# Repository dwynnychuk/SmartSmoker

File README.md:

# Smart-Smoker
Upgrade to my existing Traeger smoker BBQ to add intelligent functionality. Initial upgrades target data acquisition to monitor internal and ambient temperatures. The second stage of this project will use integrated sensor data to drive the smoker fan, auger, and hot end with a custom PID-based controller. 

# How it works
Firmware and iOS application in development. The devices will tie into the wall power on the control panel inside the smoker. An iOS device will be used to connect to the system once running, which will receive updates over BLE regarding the status of the cook. 

# Hardware
Main PCB  
- Custom implementation of ESP32-WROOM module for WiFi and BLE connectivity
- AC/DC rectifier with optional USB power handled with power path selector IC (LTC4412)
- Input for 4x K-Type thermocouples to monitor food temperature (x2), external ambient temperature, and internal ambient temperature. Analog multiplexer is used to allow the use of a single amplifier.
- Interface to connect to Lid and Hopper PCBs

Lid PCB  
- Ambient light sensor to detect if the user left the cover off after a cook
- IMU to be used as a forward feed input for the PID controller

Hopper PCB  
- Ambient light sensor to detect if the user left the cover off after a cook
- IMU to alert the user if the hopper lid is left open
- ToF sensor to read remaining pellet level

# Pinout
1 - I2C SDA  
2 - GND  
3 - I2C SCL  
4 - +3.3V  

# Image

# Suggested Changes for Next Hardware REV
- Delete 1x ambient light sensors
- Add a dedicated GND pin for easier use of a logic analyzer
- Breakout XSHUT and INT pins on main board for easier connection to hopper
- Footprint change on U4
- Add control for Traeger interface to implement PID control
- Add jumper for I2C select on IMU(s)

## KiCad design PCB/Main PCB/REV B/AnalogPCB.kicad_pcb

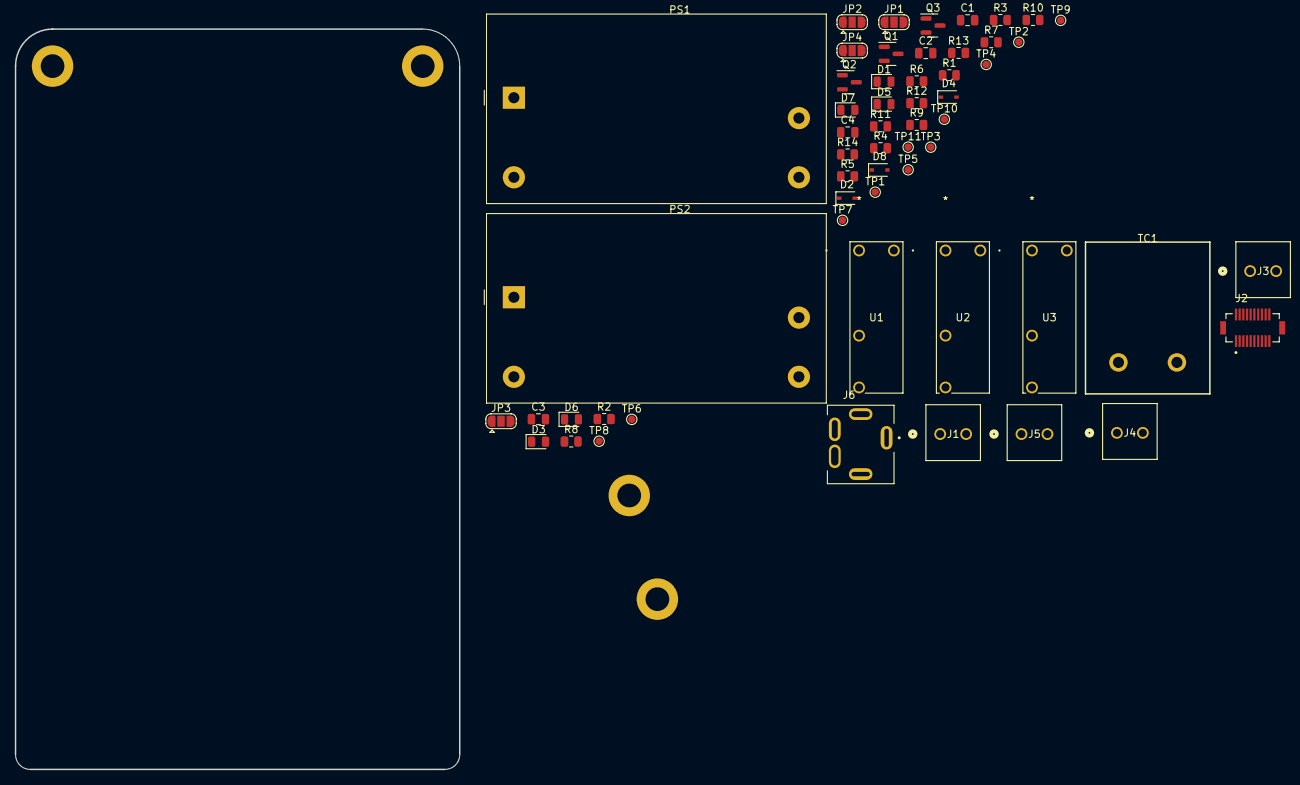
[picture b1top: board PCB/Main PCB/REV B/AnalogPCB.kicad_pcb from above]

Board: 2 copper layers, 60.0 x 100.0 mm, 60 parts (0 on the bottom side), 31 nets, no tracks yet.

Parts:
C1, C3: 0.1uF 50V X7R 0805; C_0805_2012Metric
C2, C4: 10uF 16V X5R 0805; C_0805_2012Metric
D1, D3, D7: B 3.2V 20mA 0805; LED_0805_2012Metric
D2, D4, D8: Schottky 30v 200mA; D_SOD-323
D5, D6: R 2.0V 20mA; LED_0805_2012Metric
H1, H2, H3, H4: MountingHole; MountingHole_3.2mm_M3_DIN965_Pad
J1, J3, J4, J5: 393570002; CONN_393570002_MOL
J2: DF12NB_4.0_-20DP-0.5V_51_; HRS_DF12NB_4.0_-20DP-0.5V_51_
J6: SJ3-35053D; SAMESKY_SJ3-35053D
JP1, JP2, JP3, JP4: SolderJumper_3_Open; SolderJumper-3_P1.3mm_Open_RoundedPad1.0x1.5mm
PS1: IRM-10-3.3; Converter_ACDC_MeanWell_IRM-10-xx_THT
PS2: IRM-05-5; Converter_ACDC_MeanWell_IRM-05-xx_THT
Q1, Q2, Q3: 2N7002; SOT-23
R1, R4, R9: 91Ohm 1% 0805; R_0805_2012Metric
R2, R5, R10: 10K 1% 0805; R_0805_2012Metric
R3, R6, R11: 0 Ohm 0805; R_0805_2012Metric
R7: 150Ohm 1% 0805; R_0805_2012Metric
R8: 64.9Ohm 1% 0805; R_0805_2012Metric
R12, R13, R14: 1kOhm 0.1% 0805; R_0805_2012Metric
TC1: Thermocouple_Block; K-TypeAdapter
TP1, TP2, TP3, TP4, TP5, TP6, TP7, TP8, TP9, TP10, TP11: TP; TestPoint_Pad_D1.0mm
U1, U2, U3: ALDP105W; PAN_ALD_PAN

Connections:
+3.3VA: C1.2, C2.1, J2.1, J2.3, J2.5, J2.7, JP1.3 (B), JP2.3 (B), JP3.3 (B), PS1.4 (+Vo), R8.1, R12.1, R13.1, TP4.1, TP10.1
+5V: C3.2, C4.1, D2.1 (K), D4.1 (K), D8.1 (K), J2.9, J2.11, PS2.4 (+Vo), R1.1, R4.1, R7.1, R9.1, TP5.1, U1.1, U2.1, U3.1
/AC_L: J1.1, PS1.2 (AC/L), PS2.2 (AC/L), TP3.1, U1.2, U2.2, U3.2
/AC_N: J1.2, J3.2, J4.2, J5.2, PS1.1 (AC/N), PS2.1 (AC/N), TP1.1
/Auger_+: J5.1, U1.3
/Fan_+: J4.1, U3.3
/Ignitor_+: J3.1, U2.3
/MeatProbe+: J2.19, R12.2, R14.1
/MeatProbe-: J2.20, J6.3, R13.2
/MeatProbeSleeve: J6.1, JP4.3 (B)
/MeatProbeTip: J6.2, JP4.1 (A)
/Opto_Auger: J2.15, Q1.1 (G), R2.2, TP2.1
/Opto_Fan: J2.16, Q3.1 (G), R10.2, TP9.1
/Opto_Ignitor: J2.17, Q2.1 (G), R5.2, TP6.1
/Probe1+: J2.13, TC1.1 (+)
/Probe1-: J2.14, TC1.2 (-)
GND: C1.1, C2.2, C3.1, C4.2, D5.1 (K), D6.1 (K), J2.2, J2.4, J2.6, J2.8, J2.10, J2.12, J2.18, JP1.1 (A), JP2.1 (A), JP3.1 (A), JP4.2 (C), PS1.3 (-Vo), PS2.3 (-Vo), Q1.2 (S), Q2.2 (S), Q3.2 (S), R14.2, TP11.1
unnamed: D1.1 (K), Q1.3 (D), R3.2
unnamed: D1.2 (A), R1.2
unnamed: D2.2 (A), R3.1, U1.4
unnamed: D3.2 (A), R4.2
unnamed: D5.2 (A), R7.2, TP7.1
unnamed: D7.2 (A), R9.2
unnamed: JP1.2 (C), R2.1
unnamed: JP2.2 (C), R5.1
unnamed: JP3.2 (C), R10.1
unnamed: D3.1 (K), Q2.3 (D), R6.2
unnamed: D7.1 (K), Q3.3 (D), R11.2
unnamed: D6.2 (A), R8.2, TP8.1
unnamed: D4.2 (A), R6.1, U2.4
unnamed: D8.2 (A), R11.1, U3.4

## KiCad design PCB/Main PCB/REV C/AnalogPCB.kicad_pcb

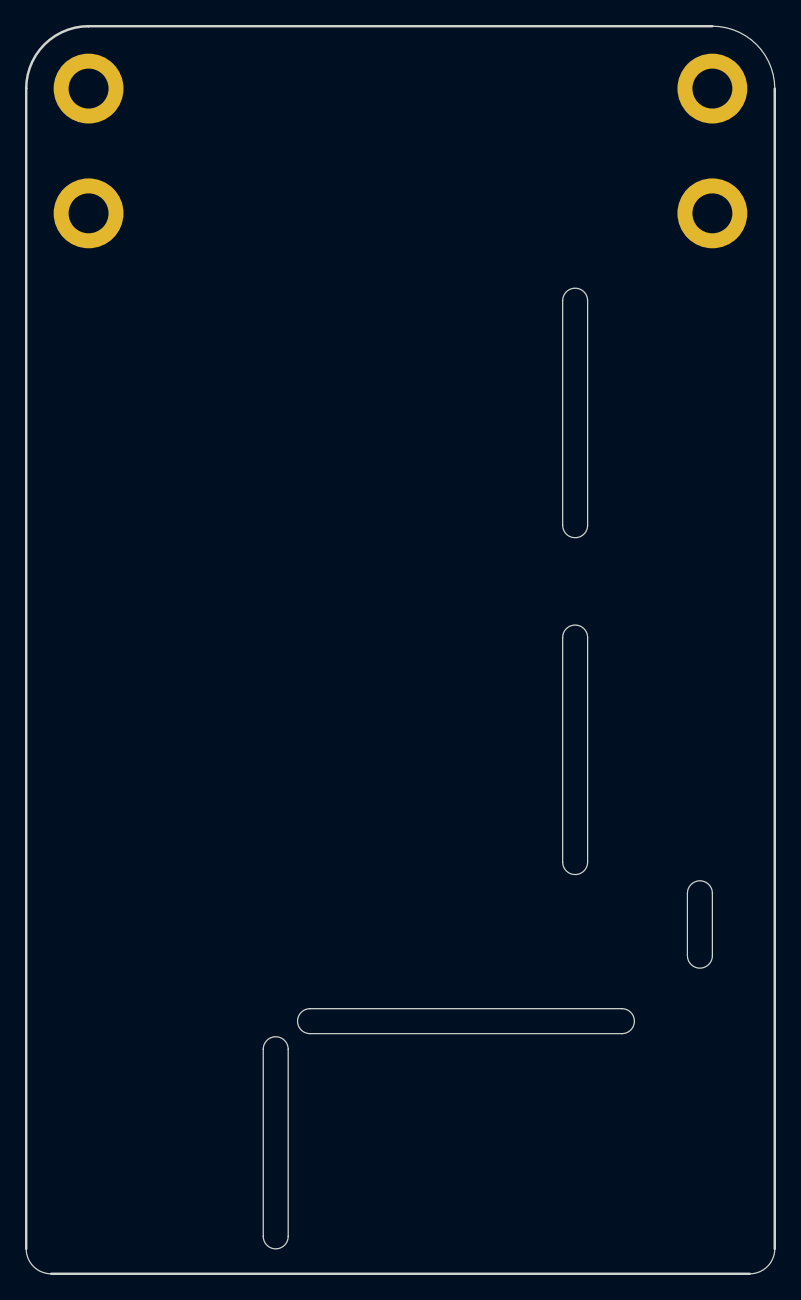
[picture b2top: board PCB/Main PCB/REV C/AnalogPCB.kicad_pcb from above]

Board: 2 copper layers, 60.0 x 100.0 mm, 5 parts (1 on the bottom side), 3 nets, no tracks yet.

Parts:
H1, H2, H3, H4: MountingHole; MountingHole_3.2mm_M3_DIN965_Pad
J2: DF12NB_4.0_-20DP-0.5V_51_; HRS_DF12NB_4.0_-20DP-0.5V_51_

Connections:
+3.3VA: J2.1, J2.3, J2.5, J2.7
+5V: J2.9, J2.11
GND: J2.2, J2.4, J2.6, J2.8, J2.10, J2.12, J2.18

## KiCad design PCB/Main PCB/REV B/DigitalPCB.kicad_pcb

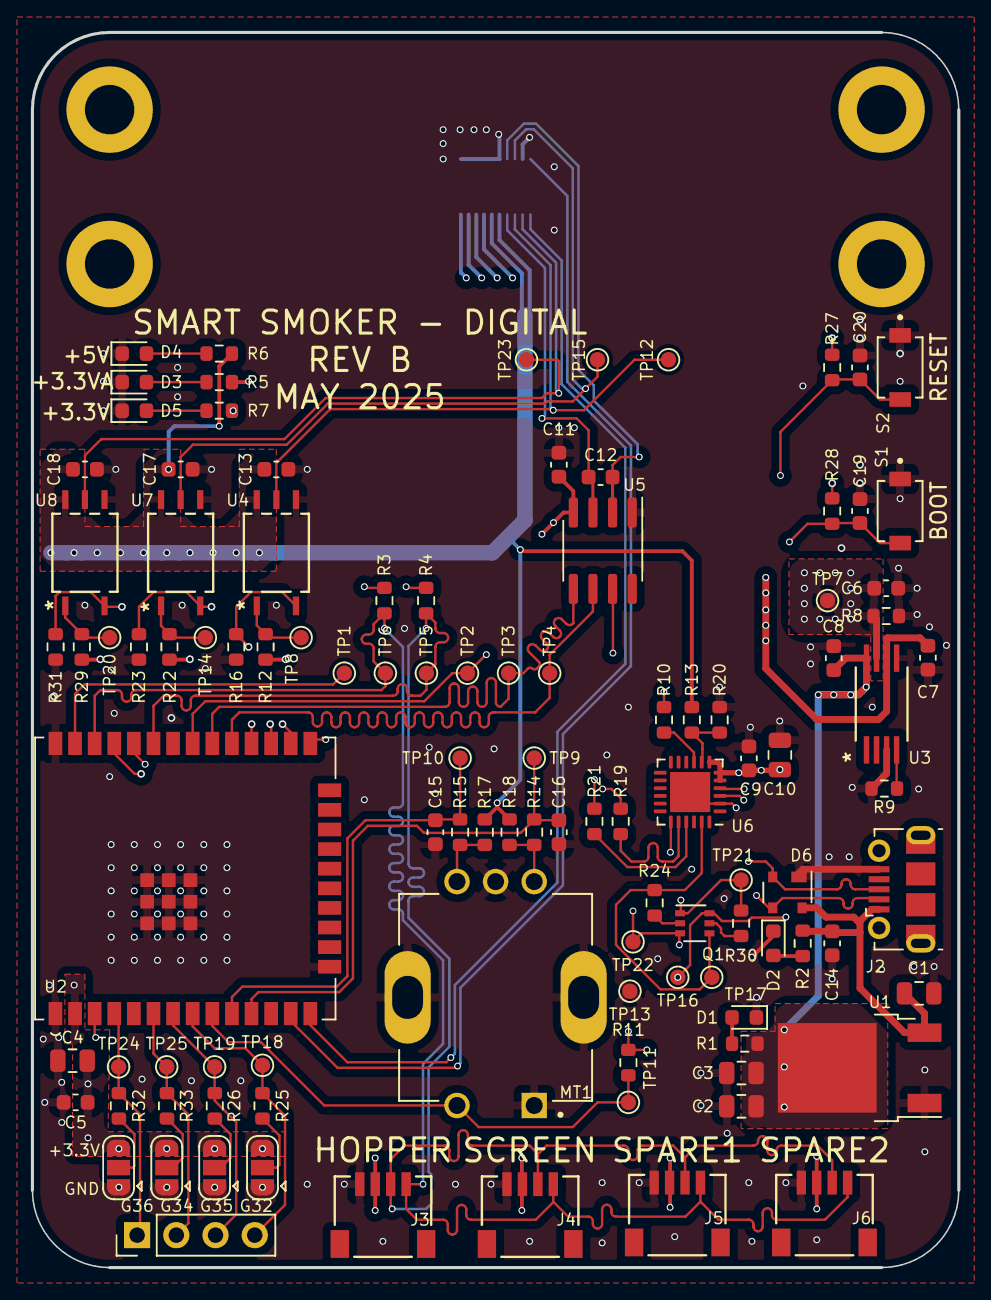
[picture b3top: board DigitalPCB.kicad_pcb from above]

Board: 4 copper layers, 60.0 x 80.0 mm, 111 parts (1 on the bottom side), 58 nets.

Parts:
C1, C2, C3: 10uF 16V X5R 0805; C_0805_2012Metric
C4: 22uF 10V X5R 0805; C_0805_2012Metric
C5, C7, C8, C9, C11, C13, C14, C17, C18, C19, C20: 0.1uF 50V X7R 0603; C_0603_1608Metric
C6: 1uF 16V X7R 0603; C_0603_1608Metric
C10: 4.7uF 25V X5R 0805; C_0805_2012Metric
C12, C15, C16: 0.01uF 50V X7R 0603; C_0603_1608Metric
D1, D2, D3, D4, D5: R 2.0V 20mA; LED_0603_1608Metric
D6: SP0503BAHT; SOT-143
H1, H2, H3, H4: MountingHole; MountingHole_3.2mm_M3_DIN965_Pad
J1: DF12NC-20DS-0.5V_51_; HRS_DF12NC-20DS-0.5V_51_
J2: 1050170001; USB_Micro-B_Molex-105017-0001
J3: Hopper; PRT-14417
J4: Screen; PRT-14417
J5: Spare1; PRT-14417
J6: Spare2; PRT-14417
JP1, JP2, JP3, JP4: SolderJumper_3_Open; SolderJumper-3_P1.3mm_Open_RoundedPad1.0x1.5mm
MT1: PEC11R-4215F-S0024; XDCR_PEC11R-4215F-S0024
Q1: MBT3904DW1; SOT-363_SC-70-6
R1, R5, R7: 64.9Ohm 1% 0603; R_0603_1608Metric
R2, R6, R12, R22, R29: 150Ohm 1% 0603; R_0603_1608Metric
R3, R4: 1.8kOhm 1% 0603; R_0603_1608Metric
R8: 50Ohm 0.1% 0603; R_0603_1608Metric
R9: 250Ohm 0.1% 0603; R_0603_1608Metric
R10: 1kOhm 1% 0603; R_0603_1608Metric
R11, R14, R15, R16, R17, R18, R23, R24, R25, R26, R27, R28, R30, R31, R32, R33: 10K 1% 0603; R_0603_1608Metric
R13: 22.1kOhm 1% 0603; R_0603_1608Metric
R19, R21: 0Ohm 0603; R_0603_1608Metric
R20: 47.5kOhm 1% 0603; R_0603_1608Metric
S1, S2: TL1015AF160QG; SW_TL1015AF160QG
TP1, TP2, TP3, TP4, TP5, TP6, TP7, TP8, TP9, TP10, TP11, TP12, TP13, TP14, TP15, TP16, TP17, TP18, TP19, TP20, TP21, TP22, TP23, TP24, TP25: TP; TestPoint_Pad_D1.0mm
TP27: GPIO MISC.; PinHeader_1x04_P2.54mm_Vertical
U1: AMS1117-3.3; TO-252-2
U2: ESP32-WROOM-32UE_16MB; ESP32-WROOM-32UE 16MB
U3: TPS2115APWR; PW8-M
U4, U7, U8: TLP2362TPR_E; TLP2362
U5: MAX31855KASA; SOIC-8_3.9x4.9mm_P1.27mm
U6: CP2102N-A02-GQFN24; QFN-24-1EP_4x4mm_P0.5mm_EP2.6x2.6mm

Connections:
+3.3V: C4.2, C5.2, C6.1, C9.2, C10.2, C11.1, J3.2, J4.2, J5.2, J6.2, JP1.3 (B), JP2.3 (B), JP3.3 (B), JP4.3 (B), R3.2, R4.2, R7.1, R8.2, R10.2, R11.2, R12.1, R22.1, R27.2, R28.2, R29.1, TP7.1, U2.2 (3V3), U3.7 (OUT), U5.4 (VCC), U6.5 (VIO), U6.6 (VDD), U6.7 (VREGIN)
+3.3VA: C7.2, J1.1, J1.3, J1.5, J1.7, R5.1, U3.6 (1N2)
+3.3VP: C2.1, C3.1, C8.2, R1.1, U1.2 (VO), U3.8 (1N1)
+5V: C13.1, C17.1, C18.1, J1.9, J1.11, R6.1, R13.1, R17.1, R18.1, U4.6 (VCC), U7.6 (VCC), U8.6 (VCC)
+5VA: C1.1, C14.1, D6.4 (K), J2.1 (VBUS), R2.1, U1.3 (VI)
/Auger: R16.1, U2.26 (IO4), U4.3 (CATHODE)
/DTR: Q1.4 (E2), R24.1, TP17.1, U6.23 (~DTR)
/EN: C20.1, Q1.6 (C1), R27.1, S2.2, TP16.1, U2.3 (EN)
/Fan: R23.1, U2.27 (IO16), U7.3 (CATHODE)
/I2C_SCL: J3.4, J4.4, J5.4, J6.4, R3.1, TP6.1, U2.36 (IO22)
/I2C_SDA: J3.3, J4.3, J5.3, J6.3, R4.1, TP5.1, U2.33 (IO21)
/IO0: C19.1, Q1.3 (C2), R28.1, S1.2, TP22.1, U2.25 (IO0)
/IO25: C15.1, R15.2, TP10.1, U2.10 (IO25)
/IO26: C16.1, R14.2, TP9.1, U2.11 (IO26)
/IO32: R25.1, TP18.1, TP27.4, U2.8 (IO32)
/IO33: MT1.2, R11.1, TP11.1, U2.9 (IO33)
/IO34: R33.1, TP25.1, TP27.2, U2.6 (IO34)
/IO35: R26.1, TP19.1, TP27.3, U2.7 (IO35)
/IO36: R32.1, TP24.1, TP27.1, U2.4 (SENSOR_VP)
/Ignitor: R31.1, U2.28 (IO17), U8.3 (CATHODE)
/MeatProbe+: J1.19, U2.14 (IO12)
/MeatProbe-: J1.20, U2.13 (IO14)
/Opto_Auger: J1.15, TP12.1, U4.5 (VO)
/Opto_Fan: J1.16, TP15.1, U7.5 (VO)
/Opto_Ignitor: J1.17, TP23.1, U8.5 (VO)
/Probe1+: C12.1, J1.13, U5.3 (T+)
/Probe1-: C12.2, J1.14, U5.2 (T-)
/RTS: Q1.1 (E1), R30.1, TP21.1, U6.19 (~RTS)
/RXD: R19.2, U6.20 (RXD)
/RXD0: R21.1, U2.34 (RXD0)
/SPI_CS: TP4.1, U2.29 (IO5), U5.6 (~CS)
/SPI_MISO: TP2.1, U2.31 (IO19), U5.7 (SO)
/SPI_MOSI: TP1.1, U2.37 (IO23)
/SPI_SCK: TP3.1, U2.30 (IO18), U5.5 (SCK)
/TXD: R21.2, U6.21 (TXD)
/TXD0: R19.1, U2.35 (TXD0)
/USB_DN: D6.3 (K), J2.2 (D-), U6.4 (D-)
/USB_DP: D6.2 (K), J2.3 (D+), U6.3 (D+)
GND: C1.2, C2.2, C3.2, C4.1, C5.1, C6.2, C7.1, C8.1, C9.1, C10.1, C11.2, C13.2, C14.2, C15.2, C16.2, C17.2, C18.2, C19.2, C20.2, D1.1 (K), D2.1 (K), D3.1 (K), D4.1 (K), D5.1 (K), D6.1 (A), J1.2, J1.4, J1.6, J1.8, J1.10, J1.12, J1.18, J2.5 (GND), J3.1, J4.1, J5.1, J6.1, JP1.1 (A), JP2.1 (A), JP3.1 (A), JP4.1 (A), MT1.1, MT1.COM, MT1.S1 (SHIELD), MT1.S2 (SHIELD), R8.1, R9.2, R16.2, R20.1, R23.2, R31.2, S1.1, S2.1, TP13.1, U1.1 (GND), U2.1 (GND), U2.15 (GND), U2.38 (GND), U2.39 (GND), U2.40 (GND), U2.41 (GND), U2.42 (GND), U2.43 (GND), U2.44 (GND), U2.45 (GND), U2.46 (GND), U2.47 (GND), U3.3 (D1), U3.5 (GND), U4.4 (GND), U5.1 (GND), U6.2 (GND), U6.25 (GND), U7.4 (GND), U8.4 (GND)
unnamed: D1.2 (A), R1.2
unnamed: D2.2 (A), R2.2
unnamed: D3.2 (A), R5.2
unnamed: D4.2 (A), R6.2
unnamed: D5.2 (A), R7.2
unnamed: JP1.2 (C), R25.2
unnamed: JP2.2 (C), R26.2
unnamed: JP3.2 (C), R32.2
unnamed: JP4.2 (C), R33.2
unnamed: MT1.A, R14.1, R18.2
unnamed: MT1.B, R15.1, R17.2
unnamed: Q1.2 (B1), R24.2
unnamed: Q1.5 (B2), R30.2
unnamed: R9.1, U3.4 (ILIM)
unnamed: R10.1, U6.9 (~RST)
unnamed: R12.2, TP8.1, U4.1 (ANODE)
unnamed: R13.2, R20.2, U6.8 (VBUS)
unnamed: R22.2, TP14.1, U7.1 (ANODE)
unnamed: R29.2, TP20.1, U8.1 (ANODE)

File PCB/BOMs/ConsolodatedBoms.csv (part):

"Source:","/Users/dallynwynnychuk/Documents/Projects/Smart Smoker/SmartSmoker/PCB/Main PCB/REV B/DigitalPCB.kicad_sch"
"Date:","2025-03-18"
"Tool:","Eeschema (6.0.11-0)"
"Generator:","/Applications/KiCad/KiCad.app/Contents/SharedSupport/plugins/bom_csv_grouped_by_value.py"
"Component Count:","113"

"Individual Components:"

"Item","Qty","Reference(s)","Value","LibPart","Footprint","Datasheet","MANUFACTURER","MAXIMUM_PACKAGE_HEIGHT","Manufacturer","Manufacturer Part Number","PARTREV","STANDARD","Vendor","Vendor Part Number"
"","","AE1","Antenna - FOR BOM ONLY","Device:Antenna","Symbol:KiCad-Logo2_5mm_SilkScreen","~","","","Pulse Electronics","W3921B0100","","","Digikey","553-W3921B0100-ND"
"","","C1","10uF 16V X5R 0805","Device:C","Capacitor_SMD:C_0805_2012Metric","~","","","Samsung Electro-Mechanics","CL21A106KOQNNNE","","","Digikey","1276-1096-1-ND"
"","","C2","10uF 16V X5R 0805","Device:C","Capacitor_SMD:C_0805_2012Metric","~","","","Samsung Electro-Mechanics","CL21A106KOQNNNE","","","Digikey","1276-1096-1-ND"
"","","C3","10uF 16V X5R 0805","Device:C","Capacitor_SMD:C_0805_2012Metric","~","","","Samsung Electro-Mechanics","CL21A106KOQNNNE","","","Digikey","1276-1096-1-ND"
"","","C4","22uF 10V X5R 0805","Device:C","Capacitor_SMD:C_0805_2012Metric","~","","","Samsung Electro-Mechanics","CL21A226MPQNNNE","","","Digikey","1276-2910-1-ND"
"","","C5","0.1uF 50V X7R 0603","Device:C","Capacitor_SMD:C_0603_1608Metric","~","","","Samsung Electro-Mechanics","CL10B104KB8NNWC","","","Digikey","1276-1935-1-ND"
"","","C6","1uF 16V X7R 0603","Device:C","Capacitor_SMD:C_0603_1608Metric","~","","","Yageo","CC0603KRX7R7BB105","","","Digikey","311-1446-1-ND"
"","","C7","0.1uF 50V X7R 0603","Device:C","Capacitor_SMD:C_0603_1608Metric","~","","","Samsung Electro-Mechanics","CL10B104KB8NNWC","","","Digikey","1276-1935-1-ND"
"","","C8","0.1uF 50V X7R 0603","Device:C","Capacitor_SMD:C_0603_1608Metric","~","","","Samsung Electro-Mechanics","CL10B104KB8NNWC","","","Digikey","1276-1935-1-ND"
"","","C9","0.1uF 50V X7R 0603","Device:C","Capacitor_SMD:C_0603_1608Metric","~","","","Samsung Electro-Mechanics","CL10B104KB8NNWC","","","Digikey","1276-1935-1-ND"
"","","C10","4.7uF 25V X5R 0805","Device:C","Capacitor_SMD:C_0805_2012Metric","~","","","Samsung Electro-Mechanics","CL21A475KAQNNNE","","","Digikey","1276-1244-1-ND"
"","","C11","0.1uF 50V X7R 0603","Device:C","Capacitor_SMD:C_0603_1608Metric","~","","","Samsung Electro-Mechanics","CL10B104KB8NNWC","","","Digikey","1276-1935-1-ND"
"","","C12","0.01uF 50V X7R 0603","Device:C","Capacitor_SMD:C_0603_1608Metric","~","","","Samsung Electro-Mechanics","CL10B103KB8NNNC","","","Digikey","1276-1009-1-ND"
"","","C13","0.1uF 50V X7R 0603","Device:C","Capacitor_SMD:C_0603_1608Metric","~","","","Samsung Electro-Mechanics","CL10B104KB8NNWC","","","Digikey","1276-1935-1-ND"
"","","C14","0.1uF 50V X7R 0603","Device:C","Capacitor_SMD:C_0603_1608Metric","~","","","Samsung Electro-Mechanics","CL10B104KB8NNWC","","","Digikey","1276-1935-1-ND"
"","","C15","0.01uF 50V X7R 0603","Device:C","Capacitor_SMD:C_0603_1608Metric","~","","","Samsung Electro-Mechanics","CL10B103KB8NNNC","","","Digikey","1276-1009-1-ND"
"","","C16","0.01uF 50V X7R 0603","Device:C","Capacitor_SMD:C_0603_1608Metric","~","","","Samsung Electro-Mechanics","CL10B103KB8NNNC","","","Digikey","1276-1009-1-ND"
"","","C17","0.1uF 50V X7R 0603","Device:C","Capacitor_SMD:C_0603_1608Metric","~","","","Samsung Electro-Mechanics","CL10B104KB8NNWC","","","Digikey","1276-1935-1-ND"
"","","C18","0.1uF 50V X7R 0603","Device:C","Capacitor_SMD:C_0603_1608Metric","~","","","Samsung Electro-Mechanics","CL10B104KB8NNWC","","","Digikey","1276-1935-1-ND"
"","","C19","0.1uF 50V X7R 0603","Device:C","Capacitor_SMD:C_0603_1608Metric","~","","","Samsung Electro-Mechanics","CL10B104KB8NNWC","","","Digikey","1276-1935-1-ND"
"","","C20","0.1uF 50V X7R 0603","Device:C","Capacitor_SMD:C_0603_1608Metric","~","","","Samsung Electro-Mechanics","CL10B104KB8NNWC","","","Digikey","1276-1935-1-ND"
"","","D1","R 2.0V 20mA","Device:LED","LED_SMD:LED_0603_1608Metric","~","","","ams-OSRAM USA INC.","LO Q976-PS-25-0-20-R18","","","Digikey","475-LOQ976-PS-25-0-20-R18CT-ND"
"","","D2","R 2.0V 20mA","Device:LED","LED_SMD:LED_0603_1608Metric","~","","","ams-OSRAM USA INC.","LO Q976-PS-25-0-20-R18","","","Digikey","475-LOQ976-PS-25-0-20-R18CT-ND"
"","","D3","R 2.0V 20mA","Device:LED","LED_SMD:LED_0603_1608Metric","~","","","ams-OSRAM USA INC.","LO Q976-PS-25-0-20-R18","","","Digikey","475-LOQ976-PS-25-0-20-R18CT-ND"
"","","D4","R 2.0V 20mA","Device:LED","LED_SMD:LED_0603_1608Metric","~","","","ams-OSRAM USA INC.","LO Q976-PS-25-0-20-R18","","","Digikey","475-LOQ976-PS-25-0-20-R18CT-ND"
"","","D5","R 2.0V 20mA","Device:LED","LED_SMD:LED_0603_1608Metric","~","","","ams-OSRAM USA INC.","LO Q976-PS-25-0-20-R18","","","Digikey","475-LOQ976-PS-25-0-20-R18CT-ND"
"","","D6","SP0503BAHT","Power_Protection:SP0503BAHT","Package_TO_SOT_SMD:SOT-143","http://www.littelfuse.com/~/media/files/littelfuse/technical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","","","Littelfuse Inc.","SP0503BAHTG","","","Digikey","F2715CT-ND"
"","","H1","MountingHole","Mechanical:MountingHole","MountingHole:MountingHole_3.2mm_M3_DIN965_Pad","~","","","","","","","",""
"","","H2","MountingHole","Mechanical:MountingHole","MountingHole:MountingHole_3.2mm_M3_DIN965_Pad","~","","","","","","","",""
"","","H3","MountingHole","Mechanical:MountingHole","MountingHole:MountingHole_3.2mm_M3_DIN965_Pad","~","","","","","","","",""
"","","H4","MountingHole","Mechanical:MountingHole","MountingHole:MountingHole_3.2mm_M3_DIN965_Pad","~","","","","","","","",""
"","","J1","DF12NC-20DS-0.5V_51_","DF12NCRCPT:DF12NC-20DS-0.5V_51_","Customs Smoker:HRS_DF12NC-20DS-0.5V_51_","","Hirose","2.9 mm","Hirose","DF12NC-20DS-0.5V(51)","Apr.1.2022","Manufacturer Recommendations","Digikey","26-DF12NC-20DS-0.5V(51)CT-ND"
"","","J2","1050170001","1051330001:1051330001","Connector_USB:USB_Micro-B_Molex-105017-0001","1050170001","","","Molex","1050170001","","","Digikey","WM1399CT-ND"
"","","J3","Hopper","PRT-14417:PRT-14417","Customs Smoker:PRT-14417","PRT-14417","","","SparkFun Electronics","PRT-14417","","","Digikey","PRT-14417-ND"
"","","J4","Screen","PRT-14417:PRT-14417","Customs Smoker:PRT-14417","PRT-14417","","","SparkFun Electronics","PRT-14417","","","Digikey","PRT-14417-ND"
"","","J5","Spare1","PRT-14417:PRT-14417","Customs Smoker:PRT-14417","PRT-14417","","","SparkFun Electronics","PRT-14417","","","Digikey","PRT-14417-ND"
"","","J6","Spare2","PRT-14417:PRT-14417","Customs Smoker:PRT-14417","PRT-14417","","","SparkFun Electronics","PRT-14417","","","Digikey","PRT-14417-ND"
"","","JP1","SolderJumper_3_Open","Jumper:SolderJumper_3_Open","Jumper:SolderJumper-3_P1.3mm_Open_RoundedPad1.0x1.5mm","~","","","","","","","",""
"","","JP2","SolderJumper_3_Open","Jumper:SolderJumper_3_Open","Jumper:SolderJumper-3_P1.3mm_Open_RoundedPad1.0x1.5mm","~","","","","","","","",""
"","","JP3","SolderJumper_3_Open","Jumper:SolderJumper_3_Open","Jumper:SolderJumper-3_P1.3mm_Open_RoundedPad1.0x1.5mm","~","","","","","","","",""
"","","JP4","SolderJumper_3_Open","Jumper:SolderJumper_3_Open","Jumper:SolderJumper-3_P1.3mm_Open_RoundedPad1.0x1.5mm","~","","","","","","","",""
"","","MT1","PEC11R-4215F-S0024","PEC11R-4215F-S0024:PEC11R-4215F-S0024","Customs Smoker:XDCR_PEC11R-4215F-S0024","","J.W.Miller/Bourns","21.5 mm","Bourns Inc.","PEC11R-4220K-S0024","Rev. 09/19","Manufacturer Recommendations","Digikey","PEC11R-4220K-S0024-ND"
"","","Q1","MBT3904DW1","Transistor_BJT:MBT3904DW1","Package_TO_SOT_SMD:SOT-363_SC-70-6","http://www.onsemi.com/pub_link/Collateral/MBT3904DW1T1-D.PDF","","","onsemi","MBT3904DW1T1G","","","digikey","MBT3904DW1T1GOSCT-ND"
"","","R1","64.9Ohm 1% 0603","Device:R_US","Resistor_SMD:R_0603_1608Metric","~","","","YAGEO","RC0603FR-0764R9L","","","Digikey","311-64.9HRCT-ND"
"","","R2","150Ohm 1% 0603","Device:R_US","Resistor_SMD:R_0603_1608Metric","~","","","YAGEO","RC0603FR-07150RL","","","Digikey","311-150HRCT-ND"
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
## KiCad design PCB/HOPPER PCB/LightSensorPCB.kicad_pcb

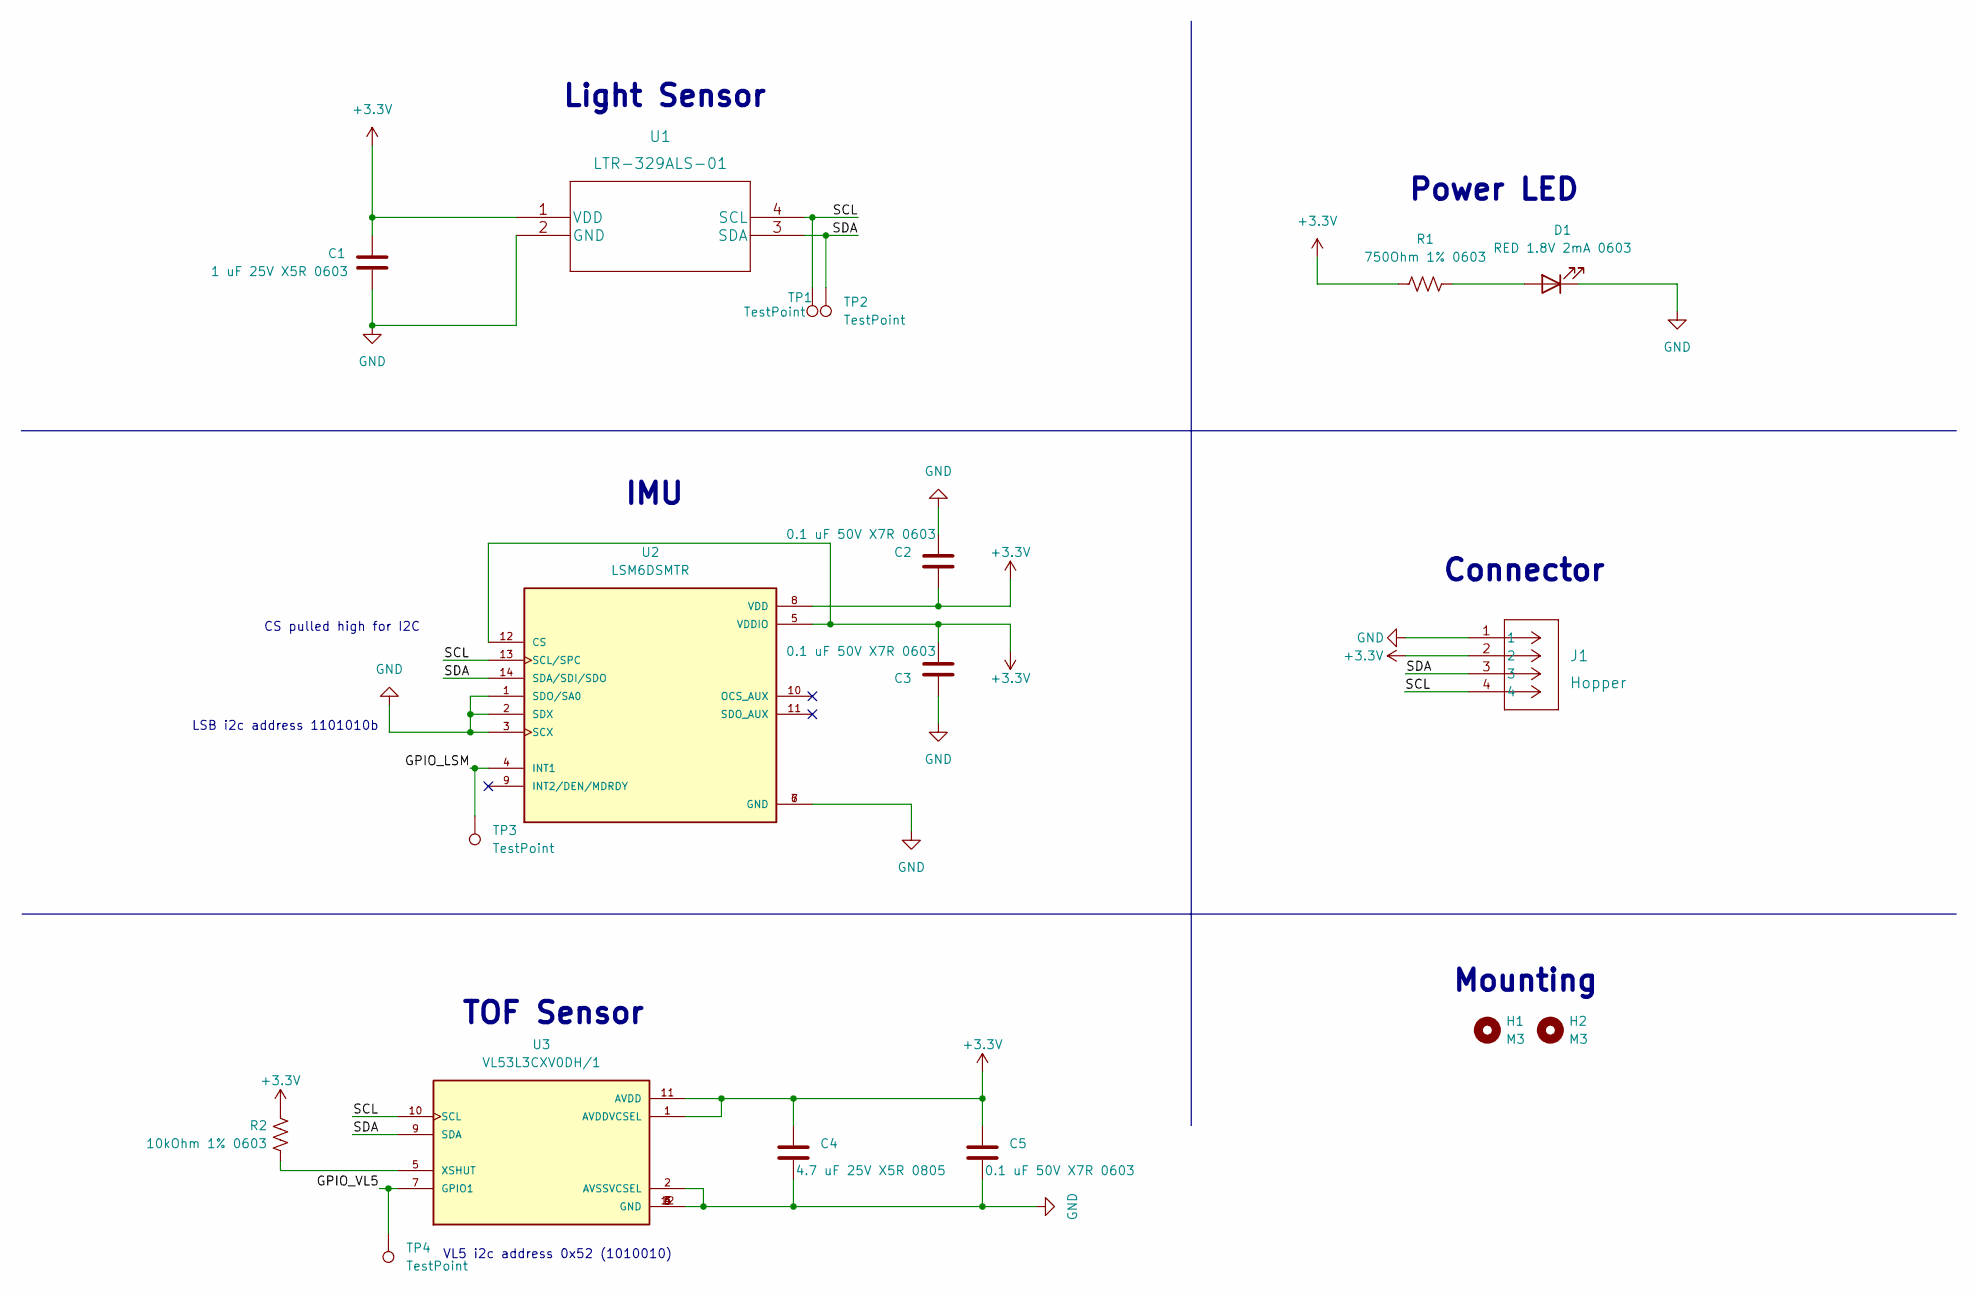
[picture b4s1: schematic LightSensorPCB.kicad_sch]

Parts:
C1: 1 uF 25V X5R 0603; C_0603_1608Metric; Manufacturer Part Number CL10A105KA8NNNC
C2, C3, C5: 0.1 uF 50V X7R 0603; C_0603_1608Metric; Manufacturer Part Number CL10B104KB8NNWC
C4: 4.7 uF 25V X5R 0805; C_0805_2012Metric; Manufacturer Part Number CL21A475KAQNNNE
D1: RED 1.8V 2mA 0603; LED_0603_1608Metric; Manufacturer Part Number CSL1901UW1
H1, H2: M3; MountingHole_3.2mm_M3_DIN965_Pad
J1: Hopper; PRT-14417; Manufacturer Part Number PRT-14417
R1: 750Ohm 1% 0603; R_0603_1608Metric; Manufacturer Part Number RC0603FR-07750RL
R2: 10kOhm 1% 0603; R_0603_1608Metric; Manufacturer Part Number RNCP0603FTD10K0
TP1, TP2, TP3, TP4: TestPoint; TestPoint_Pad_D1.0mm
U1: LTR-329ALS-01; Manufacturer Part Number LTR-329ALS-01
U2: LSM6DSMTR; PQFN50P300X250X86-14N; PARTREV Rev 7
U3: VL53L3CXV0DH/1; XDCR_VL53L3CXV0DH/1; PARTREV 2

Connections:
+3.3V: C1.1, C2.2, C3.2, C4.1, C5.1, J1.2, R1.2, R2.2, U1.1 (VDD), U2.5 (VDDIO), U2.8 (VDD), U2.12 (CS), U3.1 (AVDDVCSEL), U3.11 (AVDD)
/GPIO_LSM: TP3.1, U2.4 (INT1)
/GPIO_VL5: TP4.1, U3.7 (GPIO1)
/SCL: J1.4, TP1.1, U1.4 (SCL), U2.13 (SCL/SPC), U3.10 (SCL)
/SDA: J1.3, TP2.1, U1.3 (SDA), U2.14 (SDA/SDI/SDO), U3.9 (SDA)
GND: C1.2, C2.1, C3.1, C4.2, C5.2, D1.1 (K), J1.1, U1.2 (GND), U2.1 (SDO/SA0), U2.2 (SDX), U2.3 (SCX), U2.6 (GND), U2.7 (GND), U3.2 (AVSSVCSEL), U3.3 (GND), U3.4 (GND), U3.6 (GND), U3.12 (GND)
unnamed: D1.2 (A), R1.1
unnamed: R2.1, U3.5 (XSHUT)

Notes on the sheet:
Mounting
CS pulled high for I2C
TOF Sensor
Light Sensor
VL5 i2c address 0x52 (1010010)
LSB i2c address 1101010b
Connector
Power LED
IMU

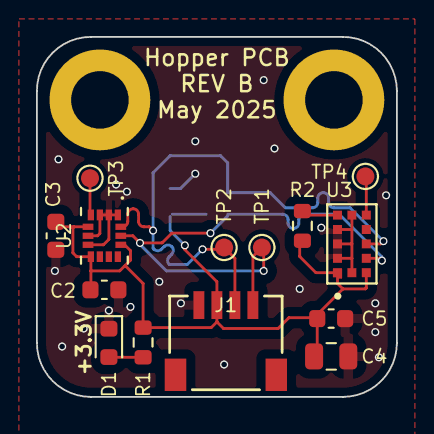
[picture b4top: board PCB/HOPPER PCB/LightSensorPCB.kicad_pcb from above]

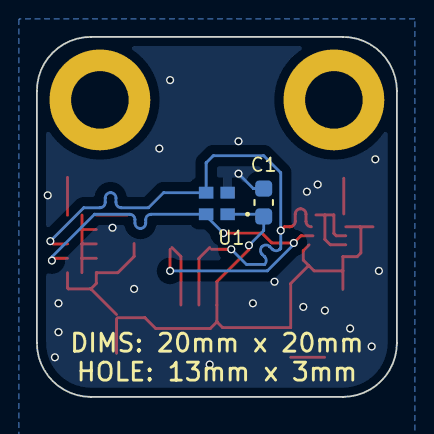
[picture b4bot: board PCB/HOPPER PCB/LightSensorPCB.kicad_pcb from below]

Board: 2 copper layers, 20.0 x 20.0 mm, 18 parts (2 on the bottom side), 8 nets.

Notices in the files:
parts and their libraries:
Copyright 2021 Accelerated Designs. All rights reserved.
